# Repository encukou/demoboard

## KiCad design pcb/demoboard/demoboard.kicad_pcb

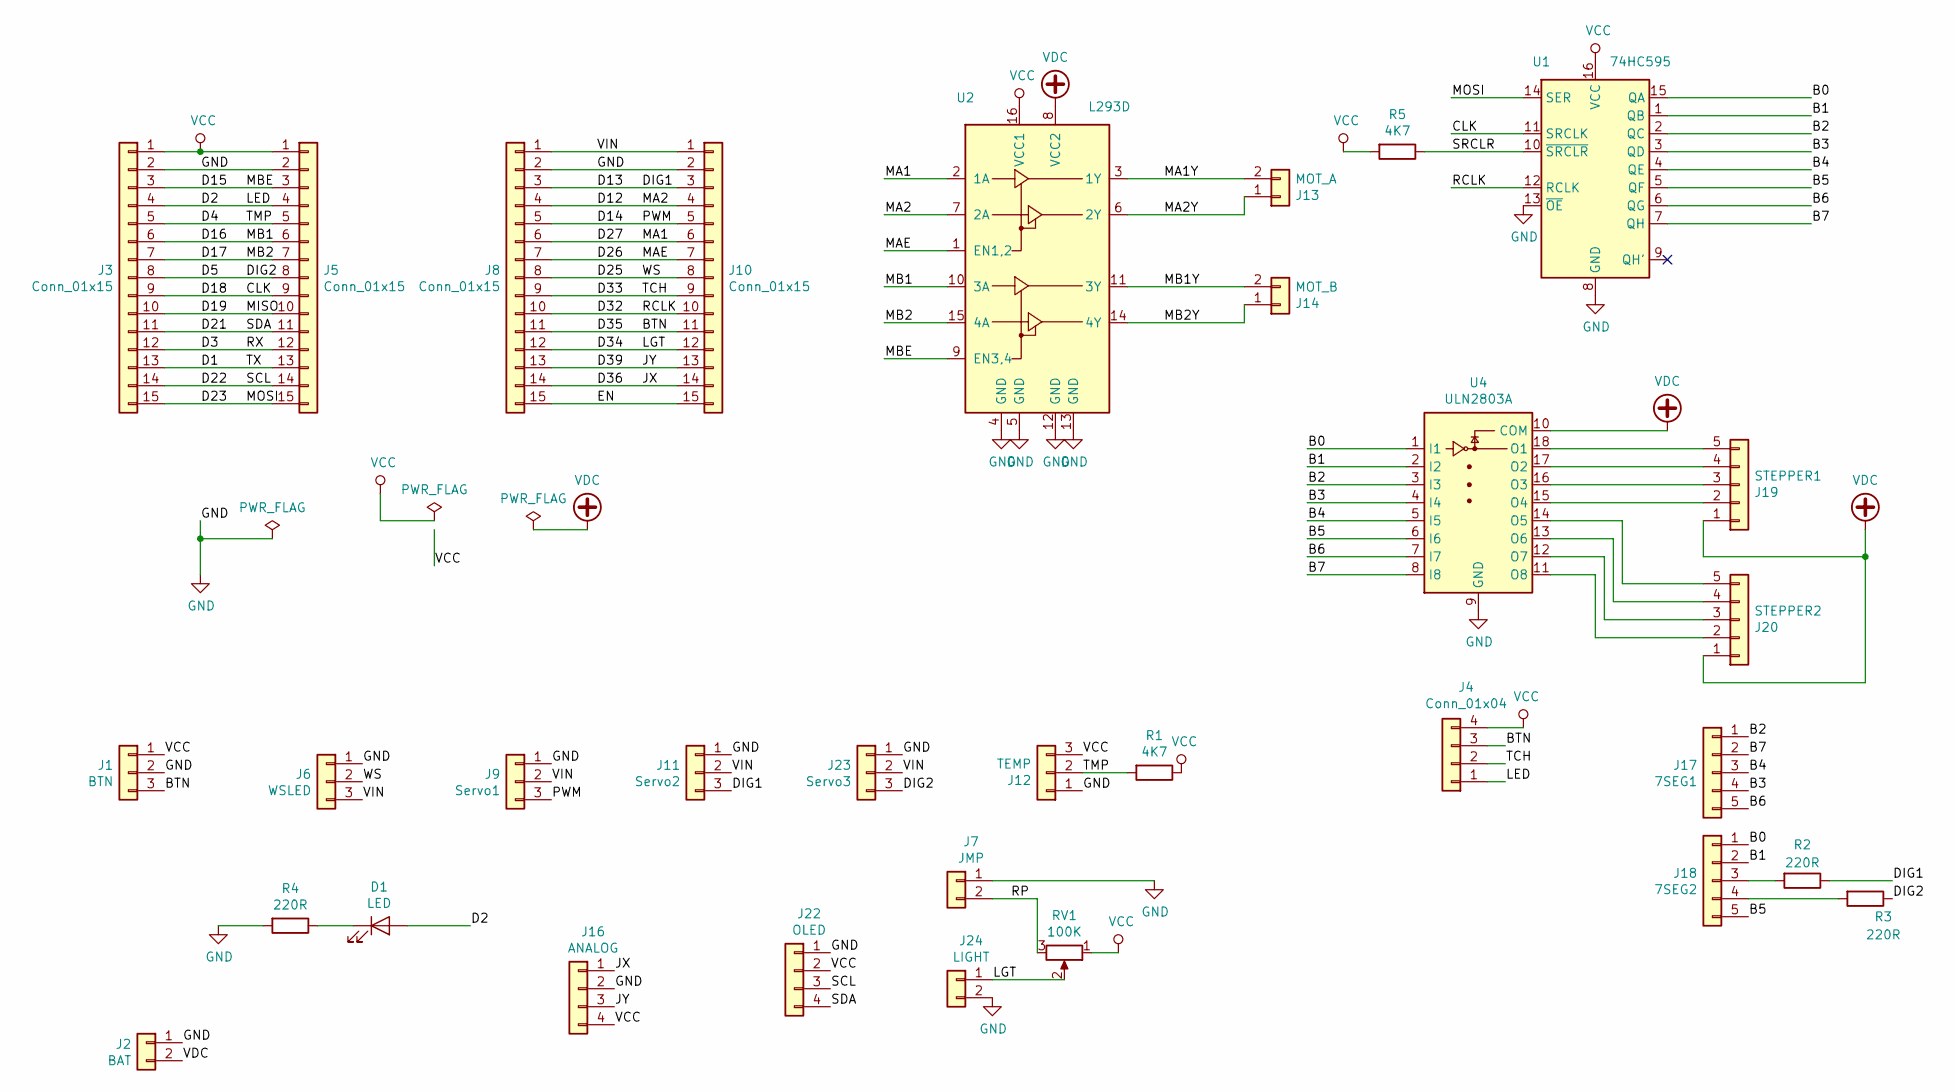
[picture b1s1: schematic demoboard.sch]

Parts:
D1: LED; LED_D3.0mm_Horizontal_O1.27mm_Z6.0mm
J1: BTN; PinSocket_1x03_P2.54mm_Horizontal
J2: BAT; JST_XH_B2B-XH-A_1x02_P2.50mm_Vertical
J3, J5, J8, J10: Conn_01x15; PinSocket_1x15_P2.54mm_Vertical
J4: Conn_01x04; PinSocket_1x04_P2.54mm_Horizontal
J6: WSLED; PinHeader_1x03_P2.54mm_Vertical
J7: JMP; PinHeader_1x02_P2.54mm_Vertical
J9: Servo1; PinHeader_1x03_P2.54mm_Vertical
J11: Servo2; PinHeader_1x03_P2.54mm_Vertical
J12: TEMP; PinSocket_1x03_P2.54mm_Vertical
J13: MOT_A; JST_XH_B2B-XH-A_1x02_P2.50mm_Vertical
J14: MOT_B; JST_XH_B2B-XH-A_1x02_P2.50mm_Vertical
J16: ANALOG; PinHeader_1x04_P2.54mm_Vertical
J17: 7SEG1; PinSocket_1x05_P2.54mm_Vertical
J18: 7SEG2; PinSocket_1x05_P2.54mm_Vertical
J19: STEPPER1; PinHeader_1x05_P2.54mm_Vertical
J20: STEPPER2; PinHeader_1x05_P2.54mm_Vertical
J22: OLED; PinSocket_1x04_P2.54mm_Vertical
J23: Servo3; PinHeader_1x03_P2.54mm_Vertical
J24: LIGHT; PinSocket_1x02_P2.54mm_Vertical
R1, R5: 4K7; R_Axial_DIN0207_L6.3mm_D2.5mm_P10.16mm_Horizontal
R2, R3: 220R; R_Axial_DIN0207_L6.3mm_D2.5mm_P2.54mm_Vertical
R4: 220R; R_Axial_DIN0207_L6.3mm_D2.5mm_P10.16mm_Horizontal
RV1: 100K; PinSocket_1x03_P2.54mm_Vertical
U1: 74HC595; DIP-16_W7.62mm
U2: L293D; DIP-16_W7.62mm
U4: ULN2803A; DIP-18_W7.62mm

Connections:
/B0: J18.1, U1.15 (QA), U4.1 (I1)
/B1: J18.2, U1.1 (QB), U4.2 (I2)
/B2: J17.1, U1.2 (QC), U4.3 (I3)
/B3: J17.4, U1.3 (QD), U4.4 (I4)
/B4: J17.3, U1.4 (QE), U4.5 (I5)
/B5: J18.5, U1.5 (QF), U4.6 (I6)
/B6: J17.5, U1.6 (QG), U4.7 (I7)
/B7: J17.2, U1.7 (QH), U4.8 (I8)
/BTN: J1.3, J4.3, J8.11, J10.11
/CLK: J3.9, J5.9, U1.11 (SRCLK)
/D1: J3.13, J5.13
/D2: D1.2 (A), J3.4, J4.1, J5.4
/D3: J3.12, J5.12
/D4: J3.5, J5.5, J12.2, R1.2
/D5: J3.8, J5.8, J23.3, R3.1
/D12: J8.4, J10.4, U2.7 (2A)
/D13: J8.3, J10.3, J11.3, R2.1
/D14: J8.5, J9.3, J10.5
/D15: J3.3, J5.3, U2.9 (EN3,4)
/D16: J3.6, J5.6, U2.10 (3A)
/D17: J3.7, J5.7, U2.15 (4A)
/D19: J3.10, J5.10
/D21: J3.11, J5.11, J22.4
/D22: J3.14, J5.14, J22.3
/D23: J3.15, J5.15, U1.14 (SER)
/D25: J6.2, J8.8, J10.8
/D26: J8.7, J10.7, U2.1 (EN1,2)
/D27: J8.6, J10.6, U2.2 (1A)
/D32: J8.10, J10.10, U1.12 (RCLK)
/D33: J4.2, J8.9, J10.9
/D34: J8.12, J10.12, J24.1, RV1.2
/D36: J8.14, J10.14, J16.1
/D39: J8.13, J10.13, J16.3
/EN: J8.15, J10.15
/MA1Y: J13.2, U2.3 (1Y)
/MA2Y: J13.1, U2.6 (2Y)
/MB1Y: J14.2, U2.11 (3Y)
/MB2Y: J14.1, U2.14 (4Y)
/RP: J7.2, RV1.3
/SRCLR: R5.1, U1.10 (~SRCLR)
/VIN: J6.3, J8.1, J9.2, J10.1, J11.2, J23.2
GND: J1.2, J2.1, J3.2, J5.2, J6.1, J7.1, J8.2, J9.1, J10.2, J11.1, J12.1, J16.2, J22.1, J23.1, J24.2, R4.2, U1.8 (GND), U1.13 (~OE), U2.4 (GND), U2.5 (GND), U2.12 (GND), U2.13 (GND), U4.9 (GND)
unnamed: D1.1 (K), R4.1
unnamed: J18.3, R2.2
unnamed: J18.4, R3.2
unnamed: J19.2, U4.15 (O4)
unnamed: J19.3, U4.16 (O3)
unnamed: J19.4, U4.17 (O2)
unnamed: J19.5, U4.18 (O1)
unnamed: J20.2, U4.11 (O8)
unnamed: J20.3, U4.12 (O7)
unnamed: J20.4, U4.13 (O6)
unnamed: J20.5, U4.14 (O5)
VCC: J1.1, J3.1, J4.4, J5.1, J12.3, J16.4, J22.2, R1.1, R5.2, RV1.1, U1.16 (VCC), U2.16 (VCC1)
VDC: J2.2, J19.1, J20.1, U2.8 (VCC2), U4.10 (COM)

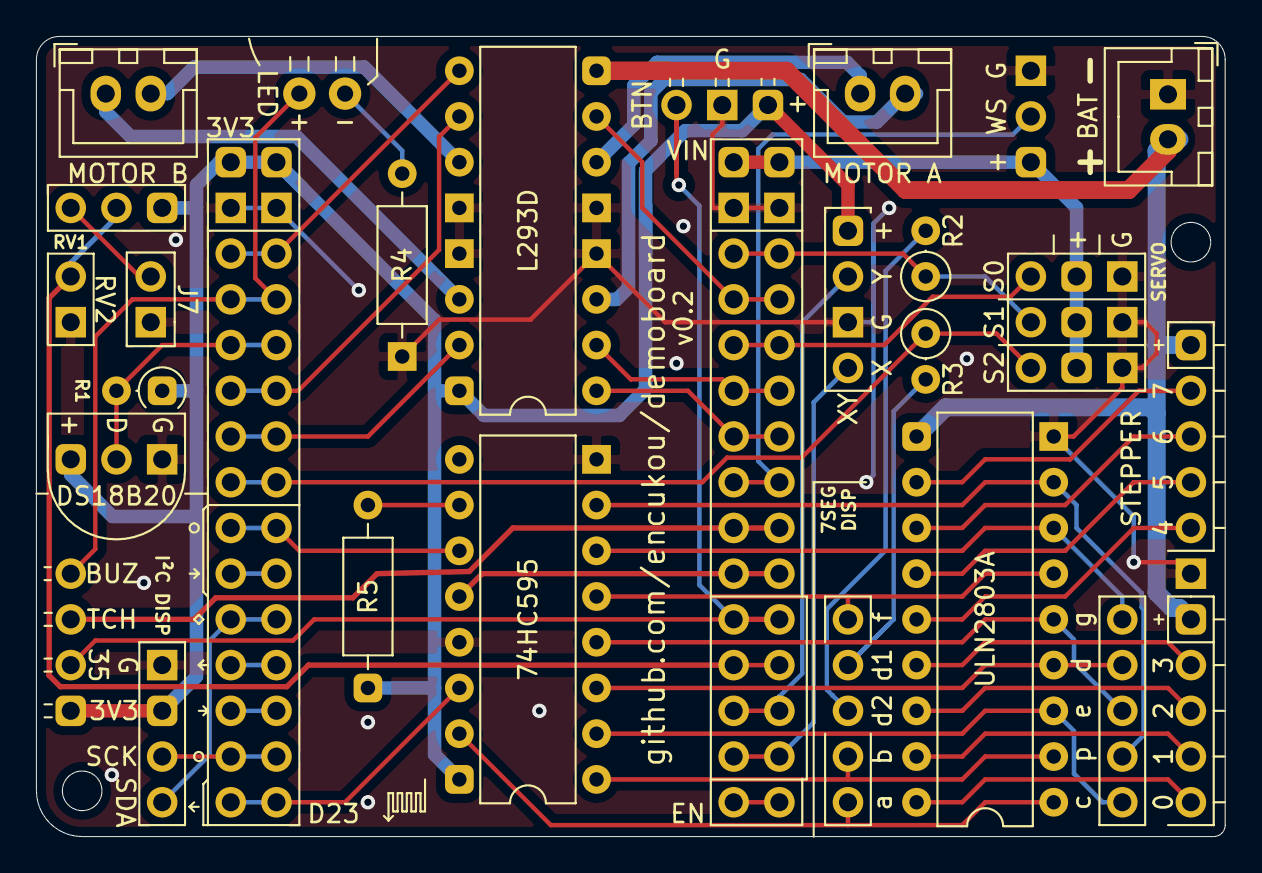
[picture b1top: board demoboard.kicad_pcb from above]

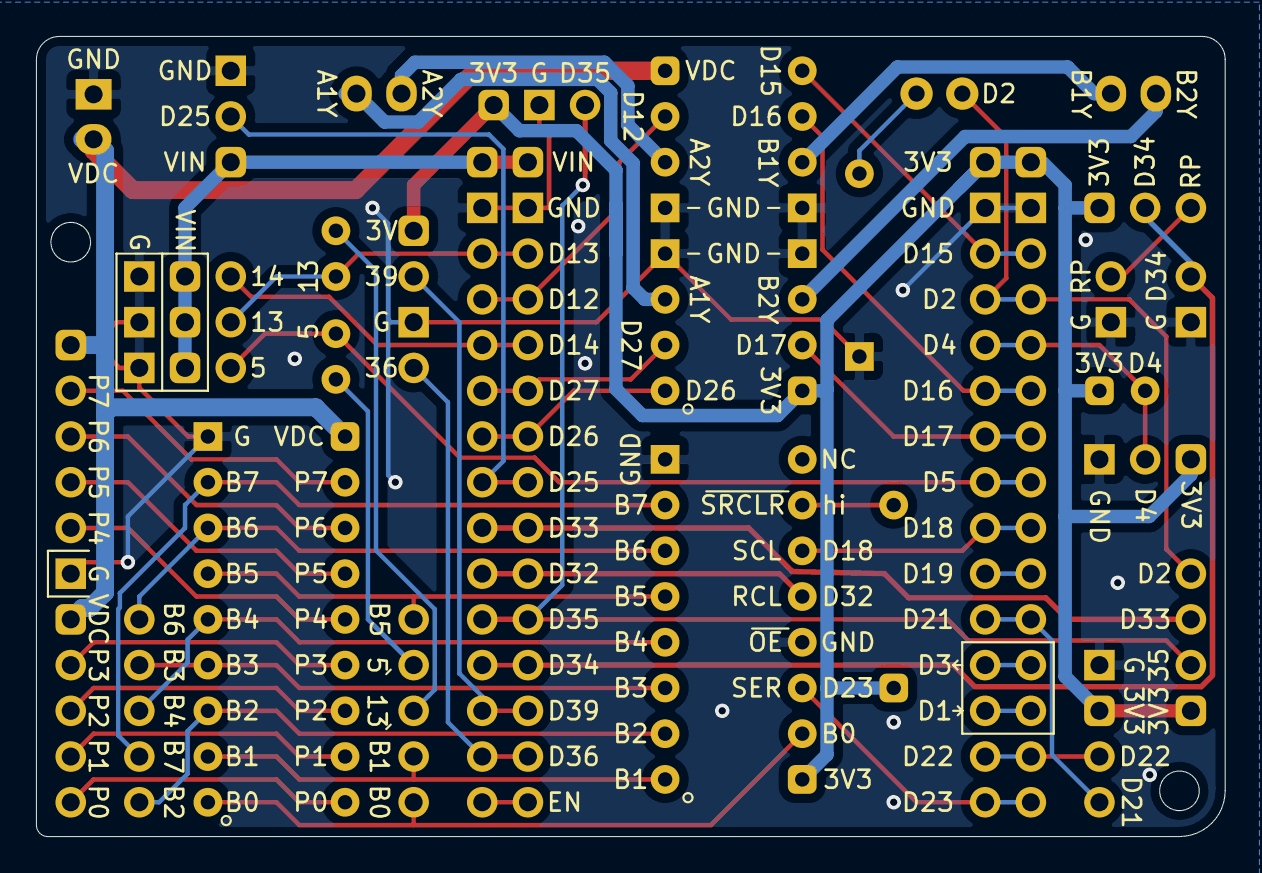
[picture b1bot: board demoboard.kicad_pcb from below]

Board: 2 copper layers, 66.0 x 44.5 mm, 32 parts (2 on the bottom side), 55 nets.

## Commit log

2020-02-16 Initial design
2020-02-16 PCB 0.1
2020-02-24 Rearrange the PCB components a bit
2020-03-01 PCB v0.2
2020-03-01 Add initial boot.py
